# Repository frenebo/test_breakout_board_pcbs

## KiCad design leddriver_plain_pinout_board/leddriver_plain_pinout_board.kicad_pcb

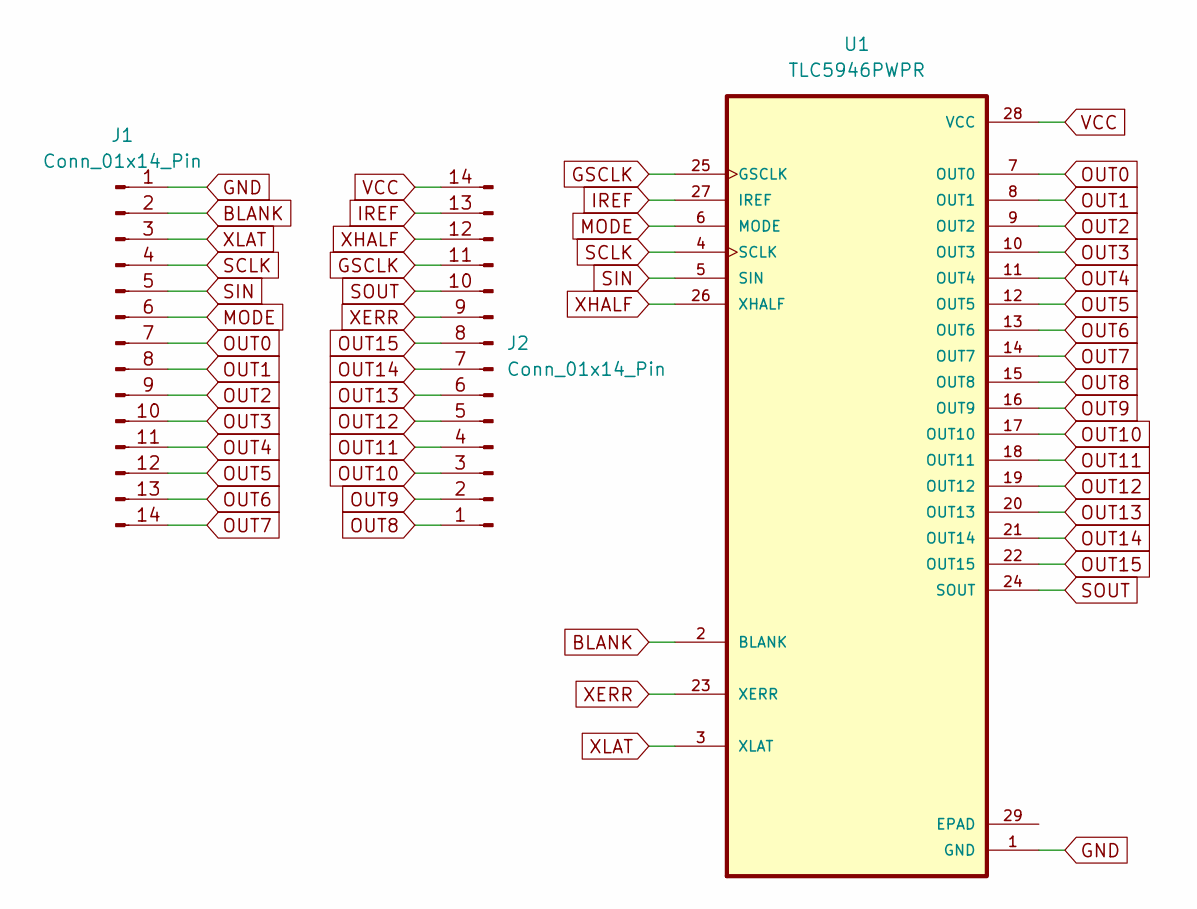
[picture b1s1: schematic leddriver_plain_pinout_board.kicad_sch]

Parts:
J1, J2: Conn_01x14_Pin; PinHeader_1x14_P2.54mm_Vertical
U1: TLC5946PWPR; IC_TPS61196PWPRQ1

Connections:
BLANK: J1.2, U1.2 (BLANK)
GND: J1.1, U1.1 (GND)
GSCLK: J2.11, U1.25 (GSCLK)
IREF: J2.13, U1.27 (IREF)
MODE: J1.6, U1.6 (MODE)
OUT0: J1.7, U1.7 (OUT0)
OUT1: J1.8, U1.8 (OUT1)
OUT2: J1.9, U1.9 (OUT2)
OUT3: J1.10, U1.10 (OUT3)
OUT4: J1.11, U1.11 (OUT4)
OUT5: J1.12, U1.12 (OUT5)
OUT6: J1.13, U1.13 (OUT6)
OUT7: J1.14, U1.14 (OUT7)
OUT8: J2.1, U1.15 (OUT8)
OUT9: J2.2, U1.16 (OUT9)
OUT10: J2.3, U1.17 (OUT10)
OUT11: J2.4, U1.18 (OUT11)
OUT12: J2.5, U1.19 (OUT12)
OUT13: J2.6, U1.20 (OUT13)
OUT14: J2.7, U1.21 (OUT14)
OUT15: J2.8, U1.22 (OUT15)
SCLK: J1.4, U1.4 (SCLK)
SIN: J1.5, U1.5 (SIN)
SOUT: J2.10, U1.24 (SOUT)
VCC: J2.14, U1.28 (VCC)
XERR: J2.9, U1.23 (XERR)
XHALF: J2.12, U1.26 (XHALF)
XLAT: J1.3, U1.3 (XLAT)

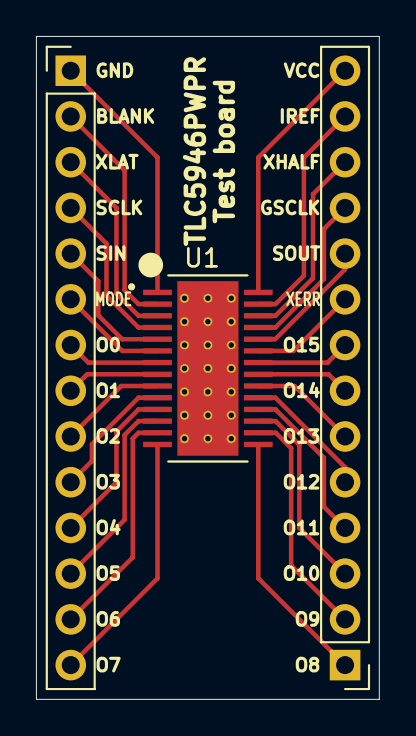
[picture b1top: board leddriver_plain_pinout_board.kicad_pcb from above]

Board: 2 copper layers, 19.1 x 36.8 mm, 3 parts (0 on the bottom side), 28 nets.

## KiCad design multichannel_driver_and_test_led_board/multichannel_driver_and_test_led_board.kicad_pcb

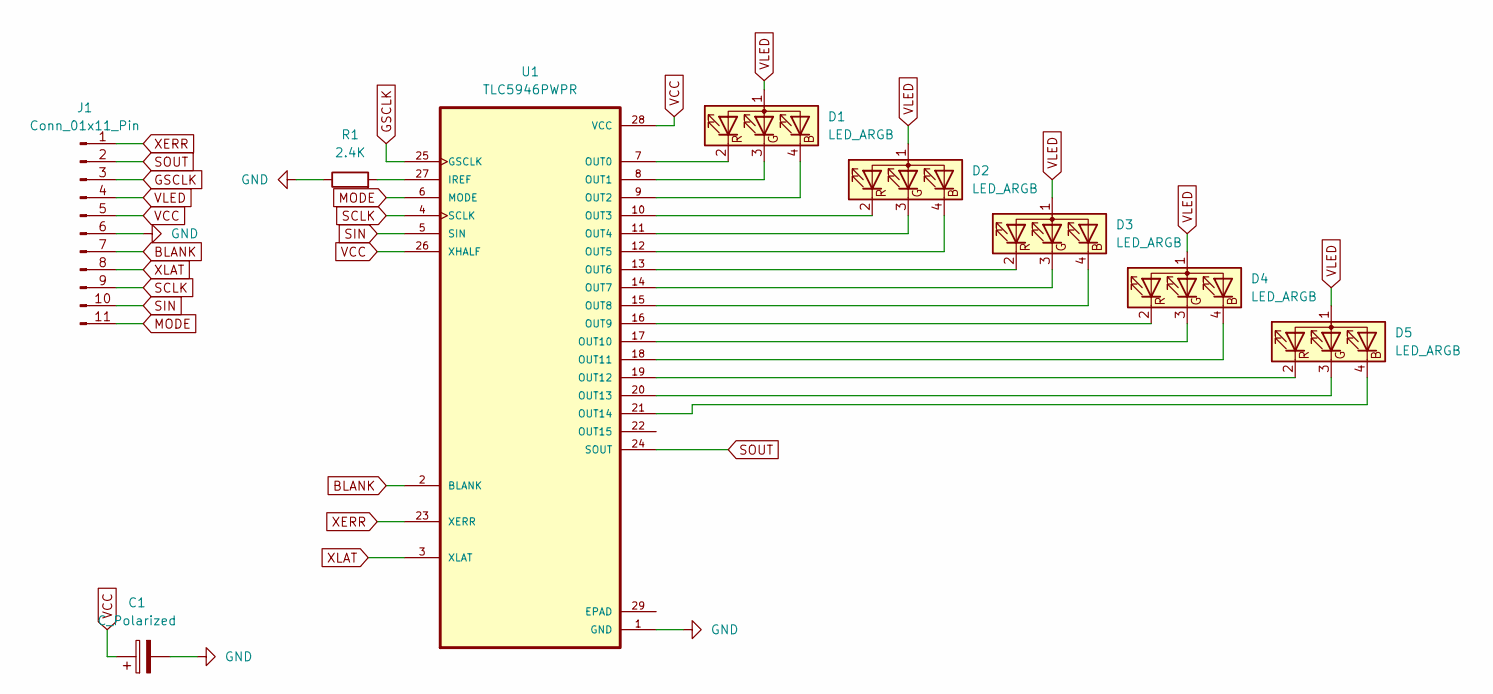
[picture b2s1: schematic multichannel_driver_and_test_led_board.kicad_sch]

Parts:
C1: C_Polarized; CP_Radial_D5.0mm_P2.50mm
D1, D2, D3, D4, D5: LED_ARGB; third leg common LED_D5.0mm-4_RGB
J1: Conn_01x11_Pin; PinHeader_1x11_P2.54mm_Vertical
R1: 2.4K; R_Axial_DIN0309_L9.0mm_D3.2mm_P15.24mm_Horizontal
U1: TLC5946PWPR

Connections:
BLANK: J1.7, U1.2 (BLANK)
GND: C1.2, J1.6, R1.1, U1.1 (GND)
GSCLK: J1.3, U1.25 (GSCLK)
MODE: J1.11, U1.6 (MODE)
unnamed: D1.4 (BK), U1.9 (OUT2)
unnamed: D1.3 (GK), U1.8 (OUT1)
unnamed: D1.2 (RK), U1.7 (OUT0)
unnamed: D2.4 (BK), U1.12 (OUT5)
unnamed: D2.3 (GK), U1.11 (OUT4)
unnamed: D2.2 (RK), U1.10 (OUT3)
unnamed: D3.4 (BK), U1.15 (OUT8)
unnamed: D3.3 (GK), U1.14 (OUT7)
unnamed: D3.2 (RK), U1.13 (OUT6)
unnamed: D4.4 (BK), U1.18 (OUT11)
unnamed: D4.3 (GK), U1.17 (OUT10)
unnamed: D4.2 (RK), U1.16 (OUT9)
unnamed: D5.4 (BK), U1.21 (OUT14)
unnamed: D5.3 (GK), U1.20 (OUT13)
unnamed: D5.2 (RK), U1.19 (OUT12)
unnamed: R1.2, U1.27 (IREF)
SCLK: J1.9, U1.4 (SCLK)
SIN: J1.10, U1.5 (SIN)
SOUT: J1.2, U1.24 (SOUT)
VCC: C1.1, J1.5, U1.26 (XHALF), U1.28 (VCC)
VLED: D1.1 (A), D2.1 (A), D3.1 (A), D4.1 (A), D5.1 (A), J1.4
XERR: J1.1, U1.23 (XERR)
XLAT: J1.8, U1.3 (XLAT)

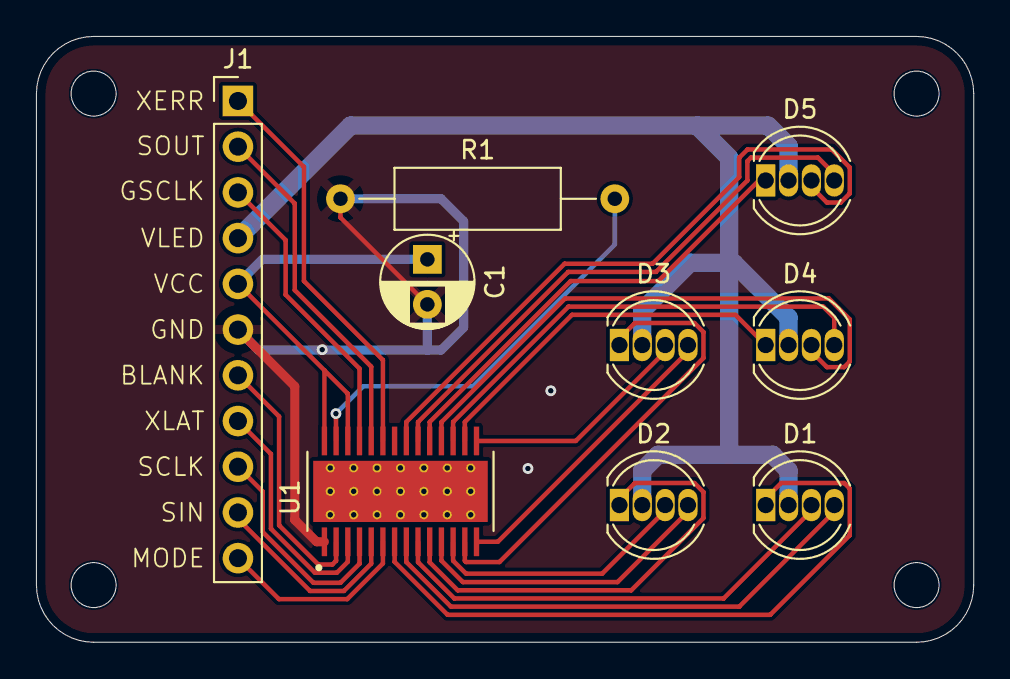
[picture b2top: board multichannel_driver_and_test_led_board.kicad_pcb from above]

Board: 2 copper layers, 52.1 x 33.7 mm, 9 parts (0 on the bottom side), 27 nets.

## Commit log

2024-03-16 adding kicad files
